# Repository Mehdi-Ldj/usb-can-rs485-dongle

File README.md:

# CAN-485 Diagnostic Gateway — Rev A

An isolated USB-C to **RS-485 / CAN 2.0B** diagnostic dongle for industrial and heavy-machinery bus work.

## Interactive design viewer

| Schematic | PCB |
|:---:|:---:|
| [Open schematic in KiCanvas →][kicanvas-sch] | [Open PCB in KiCanvas →][kicanvas-pcb] |

Read-only browser viewer — no KiCad installation required.

[kicanvas-sch]: https://kicanvas.org/?repo=https%3A%2F%2Fgithub.com%2FMehdi-Ldj%2Fusb-can-rs485-dongle%2Fblob%2Fmain%2Fhardware%2Frev-a%2FCAN485-dongle.kicad_sch
[kicanvas-pcb]: https://kicanvas.org/?repo=https%3A%2F%2Fgithub.com%2FMehdi-Ldj%2Fusb-can-rs485-dongle%2Fblob%2Fmain%2Fhardware%2Frev-a%2FCAN485-dongle.kicad_pcb

## Overview

A laptop connects through USB-C to an **STM32F072CBT6**. The board exposes an isolated
half-duplex RS-485 channel and an isolated CAN 2.0B channel on one 5-pin terminal block.
It is intended for bus diagnostics, protocol work, and field troubleshooting where the
laptop ground must not be tied to machine ground.

This is a PCB-design portfolio repository: schematic, board source, BOM, and renders.

**Firmware will be added later.** This repository currently focuses on the PCB design.

## Features

- USB 2.0 Full-Speed over USB-C
- **STM32F072CBT6** with native USB, bxCAN, and USART2
- **ADM2582E** isolated half-duplex RS-485
- **ADM3053** isolated CAN 2.0B
- Split host/field domains; no copper under the isolators
- Selectable RS-485 and CAN termination
- USB ESD, RS-485/CAN TVS, and common-mode chokes
- **73 × 33 mm, 4-layer** board
- **5-pin 3.81 mm** field terminal: GND, RS-485 A/B, CAN H/L

## Board specifications

| Item | Value |
|---|---|
| Board size | **73 × 33 mm** |
| Layers | **4**, 1.6 mm |
| Host connector | USB-C, left edge |
| Field connector | 5-pin 3.81 mm terminal, right edge |
| MCU | STM32F072CBT6 |
| RS-485 | ADM2582E, isolated, half-duplex |
| CAN | ADM3053, isolated, CAN 2.0B |
| Power | USB 5 V; TLV75533 3.3 V; isolated rails from U3/U4 |
| Planes | Split GND_HOST/GND_FIELD on In1; host +3V3 on In2 |
| Assembly | 31 BOM lines / 62 assembled parts |

## Block diagram

## Copper layers

The assembled top view with silkscreen is [`board-top.png`](docs/renders/board-top.png).
The four copper layers are:

| Layer | Image |
|---|---|
| **F.Cu** |  |
| **In1.Cu** — split GND_HOST / GND_FIELD |  |
| **In2.Cu** — host +3V3 reference |  |
| **B.Cu** |  |

## Field connector pinout

| J2 pin | Signal | Notes |
|---:|---|---|
| 1 | **GND_FIELD** | Isolated field ground |
| 2 | **RS-485_A** | Half-duplex, selectable termination |
| 3 | **RS-485_B** | Half-duplex, selectable termination |
| 4 | **CAN_H** | CAN 2.0B, selectable termination |
| 5 | **CAN_L** | CAN 2.0B, selectable termination |

The terminal block is a board-level connector. For heavy-machinery use, bring it out
through a strain-relieved pigtail or cable gland; it is not an IP-rated field connector.

## Repository structure

```text
usb-can-rs485-dongle/
├── README.md
├── docs/
│   ├── BOM.md
│   └── renders/
│       ├── block-diagram.png
│       ├── board-top.png
│       ├── board-3d-top.png
│       ├── board-3d-iso.png
│       ├── 1_board-F_Cu.png
│       ├── 2_board-In1_Cu.png
│       ├── 3_board-In2_Cu.png
│       ├── 4_board-B_Cu.png
│       └── schematic-rev-a.pdf
└── hardware/
    └── rev-a/
        ├── CAN485-dongle.kicad_pro
        ├── CAN485-dongle.kicad_sch
        ├── CAN485-dongle.kicad_pcb
        ├── CAN485-dongle.kicad_dru
        ├── CAN485-dongle-jlcpcb-bom.csv
        ├── CAN485-dongle.pretty/
        ├── symbols/
        ├── fp-lib-table
        └── sym-lib-table
```

`hardware/rev-a/` is the single canonical board. Intermediate routing copies are
local-only and excluded from the repository.

## BOM

- [`docs/BOM.md`](docs/BOM.md) — readable table
- [`hardware/rev-a/CAN485-dongle-jlcpcb-bom.csv`](hardware/rev-a/CAN485-dongle-jlcpcb-bom.csv) — JLCPCB-format CSV

**31 BOM lines / 62 assembled parts.** Key parts:

| Ref | Part | LCSC |
|---|---|---|
| U1 | STM32F072CBT6 | C81720 |
| U2 | TLV75533PDBVR | C404027 |
| U3 | ADM2582EBRWZ-REEL7 | C39494 |
| U4 | ADM3053BRWZ-REEL7 | C117821 |
| U5 | TPD4E05U06DQAR | C138714 |
| U6 | SM712.TCT | C12067 |
| J1 | USB4085-GF-A | C7095263 |
| J2 | DB2EVC-3.81-5P-GN | C395701 |

H1/H2, fiducials, test points, and solder jumpers are PCB/mechanical features and are
not in the assembly BOM.

## Getting started

1. Install **KiCad 10**.
2. Open `hardware/rev-a/CAN485-dongle.kicad_pro`.
3. Run **DRC** and inspect the board with the project libraries from `hardware/rev-a/`.

## Portfolio scope

The design source, schematic, board, BOM, and renders are included. Manufacturing
outputs — Gerbers, drill files, and CPL — are intentionally **not** part of this
portfolio repository.

## License

License not yet selected. Add one before publishing if this repository is meant to be
reused.

## Licence

Released under the [CERN Open Hardware Licence Version 2 – Permissive](LICENSE).

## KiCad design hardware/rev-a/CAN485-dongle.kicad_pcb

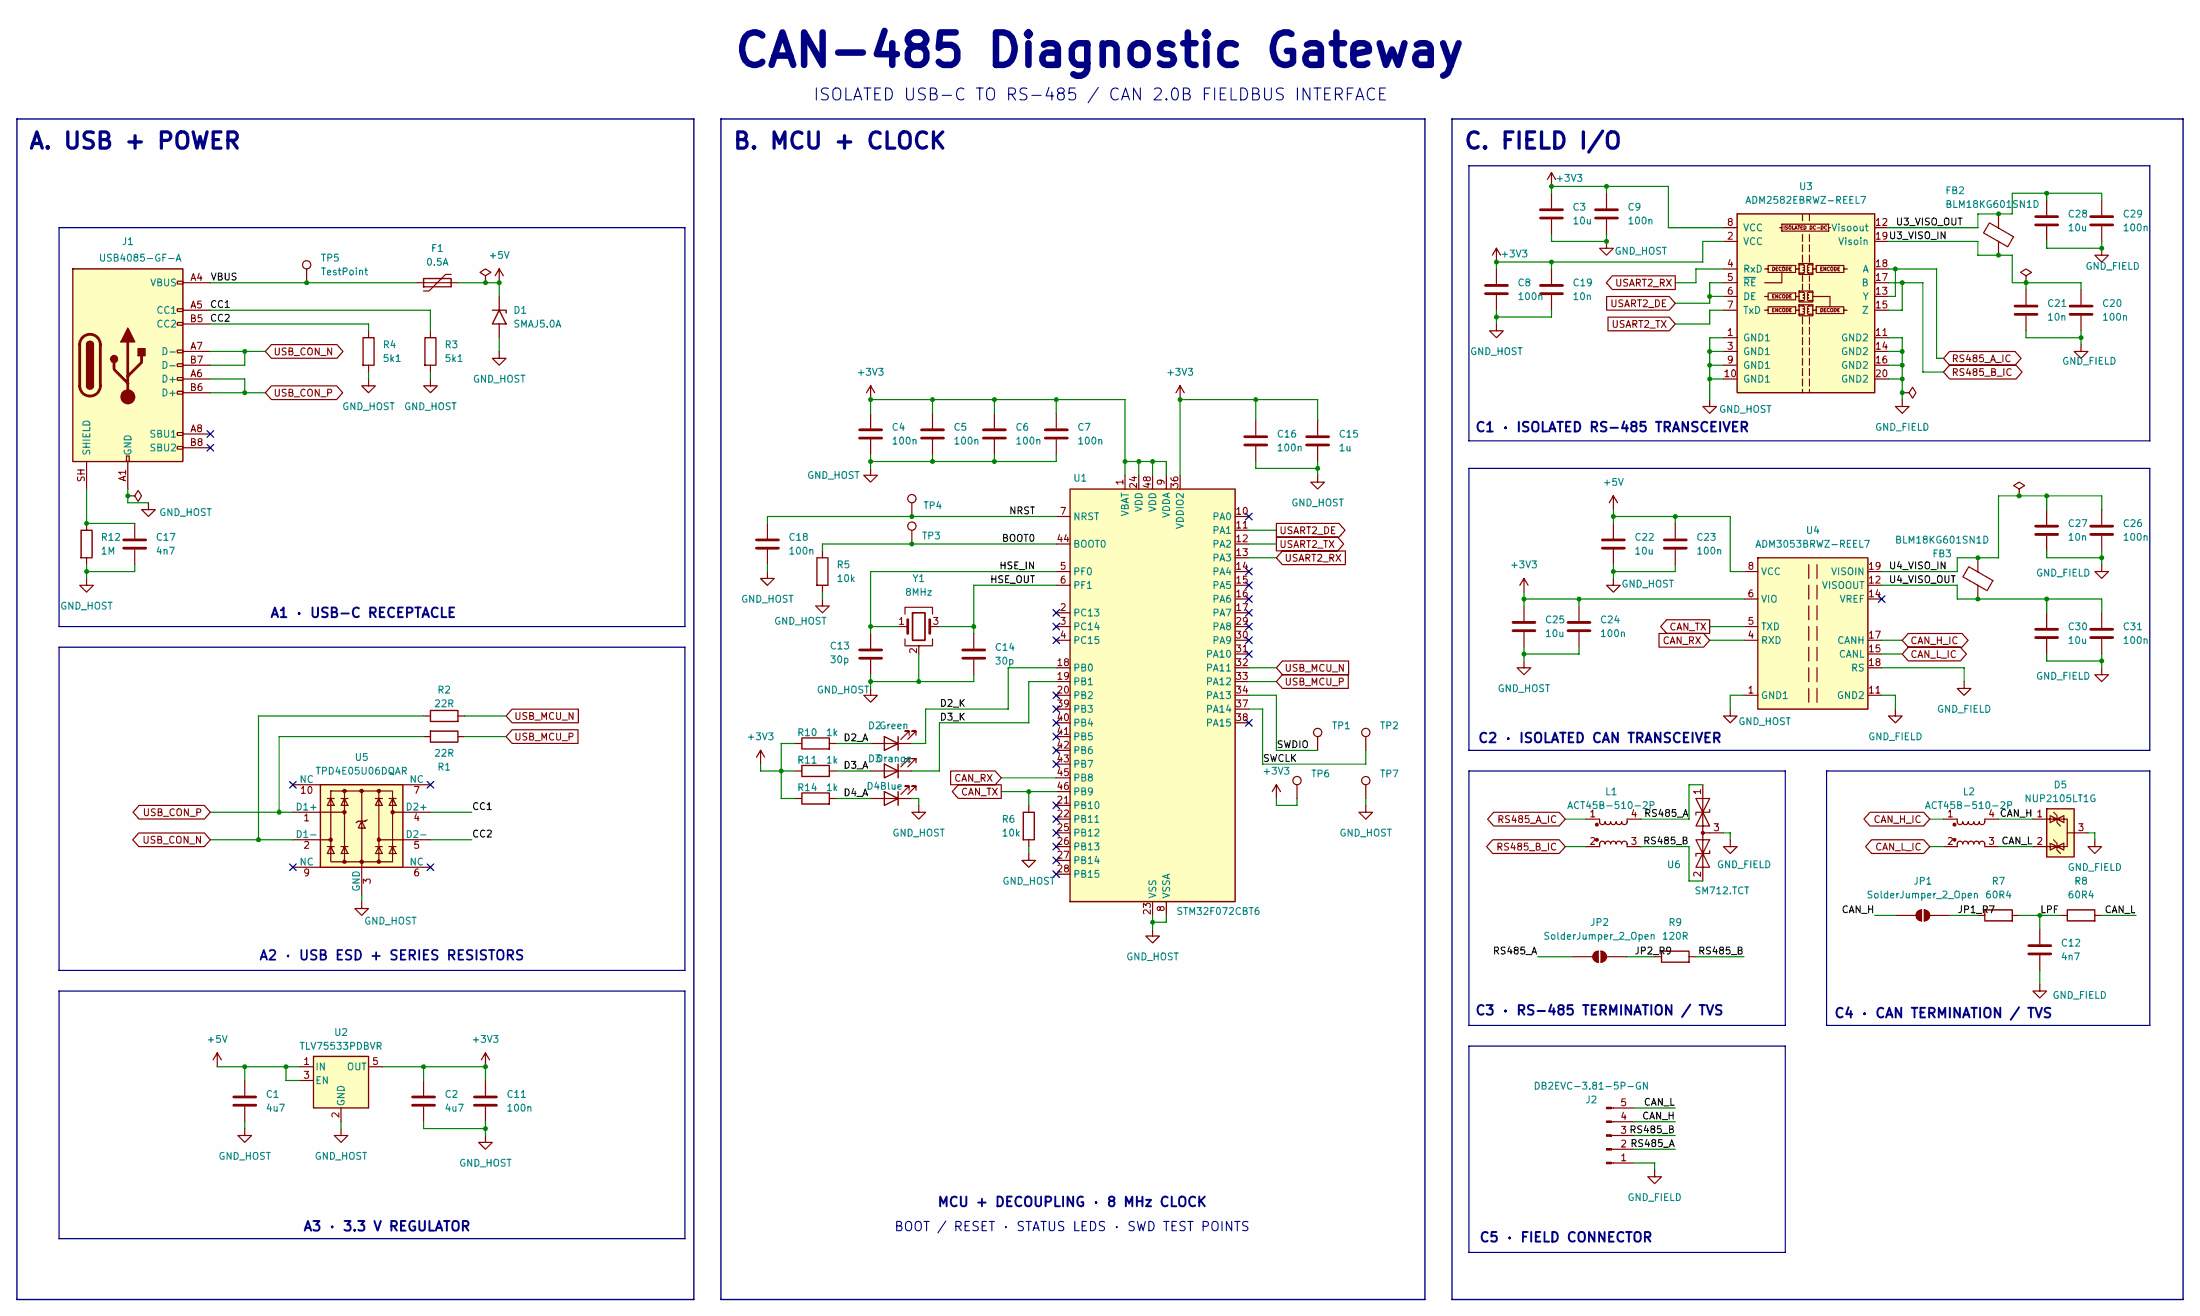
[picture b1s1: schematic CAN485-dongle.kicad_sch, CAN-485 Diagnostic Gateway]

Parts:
C1, C2: 4u7; C_0805_2012Metric; MPN CL21A475KAQNNNE; LCSC C1779
C3, C22, C25, C28, C30: 10u; C_0805_2012Metric; MPN CL21A106KAYNNNE; LCSC C15850
C4, C5, C6, C7, C8, C9, C11, C16, C18, C20, C23, C24, C26, C29, C31: 100n; C_0402_1005Metric; MPN CL05B104KO5NNNC; LCSC C1525
C12, C17: 4n7; C_0402_1005Metric; MPN 0402B472K500NT; LCSC C1538
C13, C14: 30p; C_0402_1005Metric; MPN CC0402JRNPO9BN300; LCSC C107004
C15: 1u; C_0402_1005Metric; MPN CL05A105KA5NQNC; LCSC C52923
C19, C21, C27: 10n; C_0402_1005Metric; MPN CL05B103KB5NNNC; LCSC C15195
D1: SMAJ5.0A; D_SMA; MPN SMAJ5.0A; LCSC C83329
D2: Green; LED_0805_2012Metric; MPN LTST-C171KGKT; LCSC C98224
D3: Orange; LED_0805_2012Metric; MPN LTST-C171KFKT; LCSC C284932
D4: Blue; LED_0805_2012Metric; MPN LTST-C171TBKT; LCSC C98225
D5: NUP2105LT1G; SOT-23; MPN NUP2105LT1G; LCSC C14486
F1: 0.5A; Fuse_1812_4532Metric; MPN MF-MSMF050-2; LCSC C17313
FB2, FB3: BLM18KG601SN1D; L_0603_1608Metric; MPN BLM18KG601SN1D; LCSC C85833
J1: USB4085-GF-A; USB_C_Receptacle_GCT_USB4085_Left; MPN USB4085-GF-A; LCSC C7095263
J2: DB2EVC-3.81-5P-GN; DB2EVC-3.81-5P; MPN DB2EVC-3.81-5P-GN; LCSC C395701
JP1, JP2: SolderJumper_2_Open; SolderJumper-2_P1.3mm_Open_RoundedPad1.0x1.5mm
L1, L2: ACT45B-510-2P; MPN ACT45B-510-2P-TL003; LCSC C76584
R1, R2: 22R; R_0402_1005Metric; MPN 0402WGF220JTCE; LCSC C25092
R3, R4: 5k1; R_0402_1005Metric; MPN 0402WGF5101TCE; LCSC C25905
R5, R6: 10k; R_0402_1005Metric; MPN 0402WGF1002TCE; LCSC C25744
R7, R8: 60R4; R_0603_1608Metric; MPN ERJ3EKF60R4V; LCSC C403298
R9: 120R; R_0603_1608Metric; MPN 0603WAF1200T5E; LCSC C22787
R10, R11, R14: 1k; R_0402_1005Metric; MPN 0402WGF1001TCE; LCSC C11702
R12: 1M; R_0402_1005Metric; MPN 0402WGF1004TCE; LCSC C26083
TP1, TP2, TP3, TP4, TP5, TP6, TP7: TestPoint; TestPoint_Pad_D1.0mm
U1: STM32F072CBT6; LQFP-48_7x7mm_P0.5mm; MPN STM32F072CBT6; LCSC C81720
U2: TLV75533PDBVR; SOT-23-5; MPN TLV75533PDBVR; LCSC C404027
U3: ADM2582EBRWZ-REEL7; SOIC-20W_7.5x12.8mm_P1.27mm; MPN ADM2582EBRWZ-REEL7; LCSC C39494
U4: ADM3053BRWZ-REEL7; SOIC-20W_7.5x12.8mm_P1.27mm; MPN ADM3053BRWZ-REEL7; LCSC C117821
U5: TPD4E05U06DQAR; USON-10_2.5x1.0mm_P0.5mm; MPN TPD4E05U06DQAR; LCSC C138714
U6: SM712.TCT; SOT-23; MPN SM712.TCT; LCSC C12067
Y1: 8MHz; Crystal_SMD_3225-4Pin_3.2x2.5mm; MPN XC32M4-8.000-F18LJDT; LCSC C2905353

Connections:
+3V3: C2.1, C3.1, C4.1, C5.1, C6.1, C7.1, C8.1, C9.1, C11.1, C15.1, C16.1, C19.1, C24.1, C25.1, R10.1, R11.1, R14.1, TP6.1, U1.1 (VBAT), U1.9 (VDDA), U1.24 (VDD), U1.36 (VDDIO2), U1.48 (VDD), U2.5 (OUT), U3.2 (VCC), U3.8 (VCC), U4.6 (VIO)
+5V: C1.1, C22.1, C23.1, D1.1 (A1), F1.2, U2.1 (IN), U2.3 (EN), U4.8 (VCC)
/BOOT0: R5.1, TP3.1, U1.44 (BOOT0)
/CAN_H: D5.1 (K), J2.4, JP1.1 (A), L2.4
/CAN_L: D5.2 (K), J2.5, L2.3, R8.2
/CC1: J1.A5 (CC1), R3.1, U5.4 (D2+)
/CC2: J1.B5 (CC2), R4.1, U5.5 (D2-)
/D2_A: D2.2 (A), R10.2
/D2_K: D2.1 (K), U1.18 (PB0)
/D3_A: D3.2 (A), R11.2
/D3_K: D3.1 (K), U1.19 (PB1)
/D4_A: D4.2 (A), R14.2
/HSE_IN: C13.1, U1.5 (PF0), Y1.1
/HSE_OUT: C14.1, U1.6 (PF1), Y1.3
/JP1_R7: JP1.2 (B), R7.1
/JP2_R9: JP2.2 (B), R9.1
/LPF: C12.1, R7.2, R8.1
/NRST: C18.1, TP4.1, U1.7 (NRST)
/RS485_A: J2.2, JP2.1 (A), L1.4, U6.1 (A1)
/RS485_B: J2.3, L1.3, R9.2, U6.2 (A2)
/U3_VISO_IN: C20.1, C21.1, FB2.1, U3.19 (Visoin)
/U3_VISO_OUT: C28.1, C29.1, FB2.2, U3.12 (Visoout)
/U4_VISO_IN: C26.1, C27.1, FB3.2, U4.19 (VISOIN)
/U4_VISO_OUT: C30.1, C31.1, FB3.1, U4.12 (VISOOUT)
/VBUS: F1.1, J1.A4 (VBUS), J1.A9 (VBUS), J1.B4 (VBUS), J1.B9 (VBUS), TP5.1
CAN_H_IC: L2.1, U4.17 (CANH)
CAN_L_IC: L2.2, U4.15 (CANL)
CAN_RX: U1.45 (PB8), U4.4 (RXD)
CAN_TX: R6.1, U1.46 (PB9), U4.5 (TXD)
GND_FIELD: C12.2, C20.2, C21.2, C26.2, C27.2, C28.2, C29.2, C30.2, C31.2, D5.3 (A), J2.1, U3.11 (GND2), U3.14 (GND2), U3.16 (GND2), U3.20 (GND2), U4.11 (GND2), U4.13 (GND2), U4.16 (GND2), U4.18 (RS), U4.20 (GND2), U6.3 (common)
GND_HOST: C1.2, C2.2, C3.2, C4.2, C5.2, C6.2, C7.2, C8.2, C9.2, C11.2, C13.2, C14.2, C15.2, C16.2, C17.2, C18.2, C19.2, C22.2, C23.2, C24.2, C25.2, D1.2 (A2), D4.1 (K), J1.A1 (GND), J1.A12 (GND), J1.B1 (GND), J1.B12 (GND), R3.2, R4.2, R5.2, R6.2, R12.2, TP7.1, U1.8 (VSSA), U1.23 (VSS), U1.35 (VSS), U1.47 (VSS), U2.2 (GND), U3.1 (GND1), U3.3 (GND1), U3.9 (GND1), U3.10 (GND1), U4.1 (GND1), U4.3 (GND1), U4.7 (GND1), U4.9 (GND1), U4.10 (GND1), U5.3 (GND), U5.8 (GND), Y1.2 (G), Y1.4 (G)
unnamed: C17.1, J1.SH (SHIELD), R12.1
RS485_A_IC: L1.1, U3.13 (Y), U3.18 (A)
RS485_B_IC: L1.2, U3.15 (Z), U3.17 (B)
USART2_DE: U1.11 (PA1), U3.5 (~RE), U3.6 (DE)
USART2_RX: U1.13 (PA3), U3.4 (RxD)
USART2_TX: U1.12 (PA2), U3.7 (TxD)
USB_CON_N: J1.A7 (D-), J1.B7 (D-), R2.1, U5.2 (D1-)
USB_CON_P: J1.A6 (D+), J1.B6 (D+), R1.2, U5.1 (D1+)
USB_MCU_N: R2.2, U1.32 (PA11)
USB_MCU_P: R1.1, U1.33 (PA12)

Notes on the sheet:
ISOLATED USB-C TO RS-485 / CAN 2.0B FIELDBUS INTERFACE
B. MCU + CLOCK
CAN-485 Diagnostic Gateway
C5 · FIELD CONNECTOR
C1 · ISOLATED RS-485 TRANSCEIVER
C3 · RS-485 TERMINATION / TVS
A3 · 3.3 V REGULATOR
MCU + DECOUPLING · 8 MHz CLOCK
C. FIELD I/O
BOOT / RESET · STATUS LEDS · SWD TEST POINTS
C4 · CAN TERMINATION / TVS
A2 · USB ESD + SERIES RESISTORS
A. USB + POWER
A1 · USB-C RECEPTACLE
C2 · ISOLATED CAN TRANSCEIVER

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
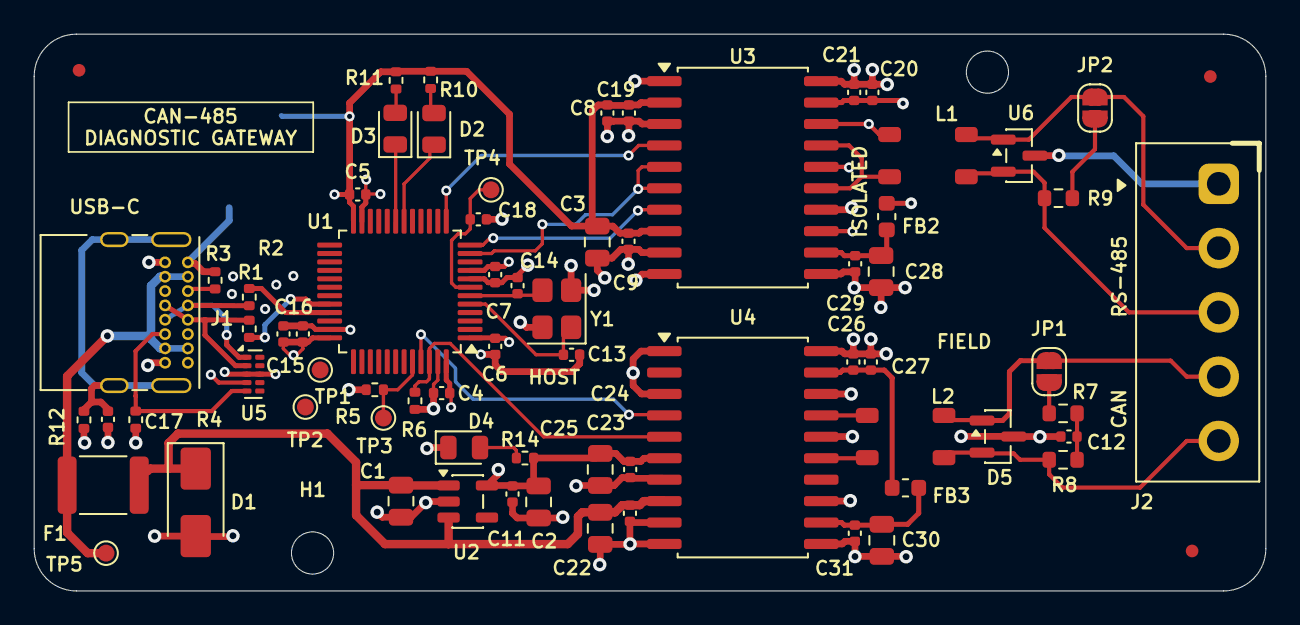
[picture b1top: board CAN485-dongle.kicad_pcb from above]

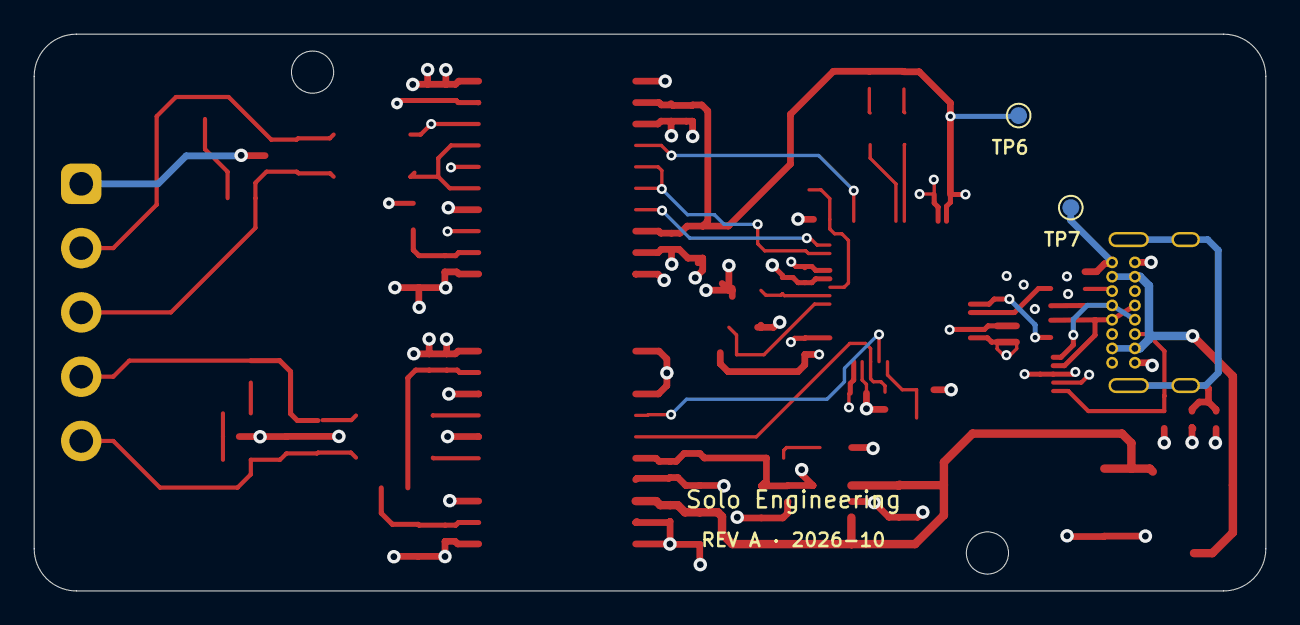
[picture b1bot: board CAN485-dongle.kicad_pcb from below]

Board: 4 copper layers, 73.0 x 33.0 mm, 76 parts (2 on the bottom side), 41 nets.

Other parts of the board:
FID1, FID2, FID3: Fiducial_0.75mm_Mask1.5mm
H1, H2: MountingHole_2.5mm_Boss5

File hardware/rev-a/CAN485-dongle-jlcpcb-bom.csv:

Comment,Designator,Footprint,LCSC Part #,MPN,Manufacturer
4u7,"C1,C2",Capacitor_SMD:C_0805_2012Metric,C1779,CL21A475KAQNNNE,Samsung
100n,"C4,C5,C6,C7,C8,C9,C11,C16,C18,C20,C23,C24,C26,C29,C31",Capacitor_SMD:C_0402_1005Metric,C1525,CL05B104KO5NNNC,Samsung
4n7,"C12,C17",Capacitor_SMD:C_0402_1005Metric,C1538,0402B472K500NT,FH
30p,"C13,C14",Capacitor_SMD:C_0402_1005Metric,C107004,CC0402JRNPO9BN300,YAGEO
1u,C15,Capacitor_SMD:C_0402_1005Metric,C52923,CL05A105KA5NQNC,Samsung
10n,"C19,C21,C27",Capacitor_SMD:C_0402_1005Metric,C15195,CL05B103KB5NNNC,Samsung
10u,"C3,C22,C25,C28,C30",Capacitor_SMD:C_0805_2012Metric,C15850,CL21A106KAYNNNE,Samsung
SMAJ5.0A,D1,Diode_SMD:D_SMA,C83329,SMAJ5.0A,Littelfuse
Green,D2,LED_SMD:LED_0805_2012Metric,C98224,LTST-C171KGKT,Lite-On
Orange,D3,LED_SMD:LED_0805_2012Metric,C284932,LTST-C171KFKT,Lite-On
Blue,D4,LED_SMD:LED_0805_2012Metric,C98225,LTST-C171TBKT,Lite-On
NUP2105LT1G,D5,Package_TO_SOT_SMD:SOT-23,C14486,NUP2105LT1G,onsemi
0.5A,F1,CAN485-dongle:Fuse_1812_4532Metric,C17313,MF-MSMF050-2,Bourns
BLM18KG601SN1D,"FB2,FB3",Inductor_SMD:L_0603_1608Metric,C85833,BLM18KG601SN1D,Murata
USB4085-GF-A,J1,CAN485-dongle:USB_C_Receptacle_GCT_USB4085_Left,C7095263,USB4085-GF-A,GCT
DB2EVC-3.81-5P-GN,J2,CAN485-dongle:DB2EVC-3.81-5P,C395701,DB2EVC-3.81-5P-GN,DORABO
ACT45B-510-2P,"L1,L2",CAN485-dongle:ACT45B-510-2P,C76584,ACT45B-510-2P-TL003,TDK
22R,"R1,R2",Resistor_SMD:R_0402_1005Metric,C25092,0402WGF220JTCE,UNI-ROYAL
5k1,"R3,R4",Resistor_SMD:R_0402_1005Metric,C25905,0402WGF5101TCE,UNI-ROYAL
10k,"R5,R6",Resistor_SMD:R_0402_1005Metric,C25744,0402WGF1002TCE,UNI-ROYAL
60R4,"R7,R8",Resistor_SMD:R_0603_1608Metric,C403298,ERJ3EKF60R4V,Panasonic
120R,R9,Resistor_SMD:R_0603_1608Metric,C22787,0603WAF1200T5E,UNI-ROYAL
1k,"R10,R11,R14",Resistor_SMD:R_0402_1005Metric,C11702,0402WGF1001TCE,UNI-ROYAL
1M,R12,Resistor_SMD:R_0402_1005Metric,C26083,0402WGF1004TCE,UNI-ROYAL
STM32F072CBT6,U1,Package_QFP:LQFP-48_7x7mm_P0.5mm,C81720,STM32F072CBT6,STMicroelectronics
TLV75533PDBVR,U2,Package_TO_SOT_SMD:SOT-23-5,C404027,TLV75533PDBVR,Texas Instruments
ADM2582EBRWZ-REEL7,U3,Package_SO:SOIC-20W_7.5x12.8mm_P1.27mm,C39494,ADM2582EBRWZ-REEL7,Analog Devices
ADM3053BRWZ-REEL7,U4,Package_SO:SOIC-20W_7.5x12.8mm_P1.27mm,C117821,ADM3053BRWZ-REEL7,Analog Devices
TPD4E05U06DQAR,U5,Package_SON:USON-10_2.5x1.0mm_P0.5mm,C138714,TPD4E05U06DQAR,Texas Instruments
SM712.TCT,U6,Package_TO_SOT_SMD:SOT-23,C12067,SM712.TCT,Semtech
8MHz,Y1,Crystal:Crystal_SMD_3225-4Pin_3.2x2.5mm,C2905353,XC32M4-8.000-F18LJDT,HCI
